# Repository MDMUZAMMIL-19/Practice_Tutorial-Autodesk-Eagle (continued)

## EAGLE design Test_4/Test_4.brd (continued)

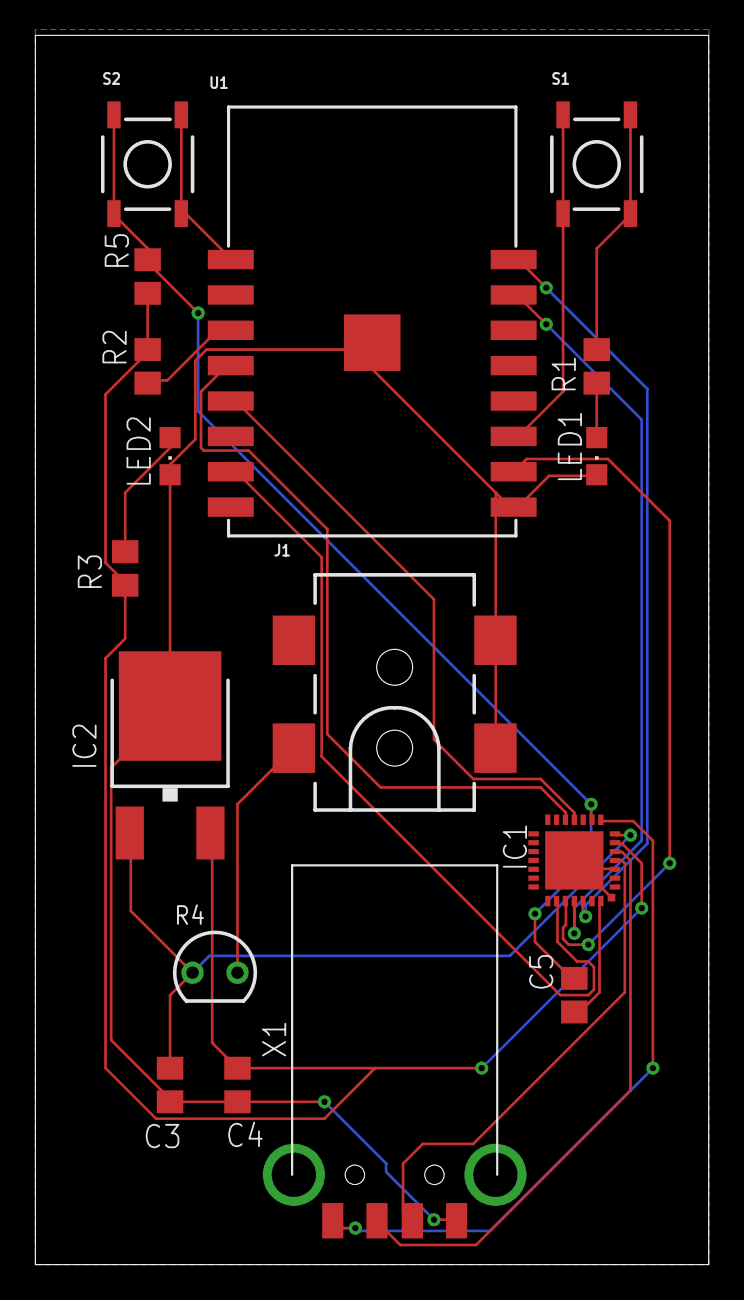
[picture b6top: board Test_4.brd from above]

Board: 2 copper layers, 38.1 x 69.5 mm, 17 parts (0 on the bottom side), 22 nets.

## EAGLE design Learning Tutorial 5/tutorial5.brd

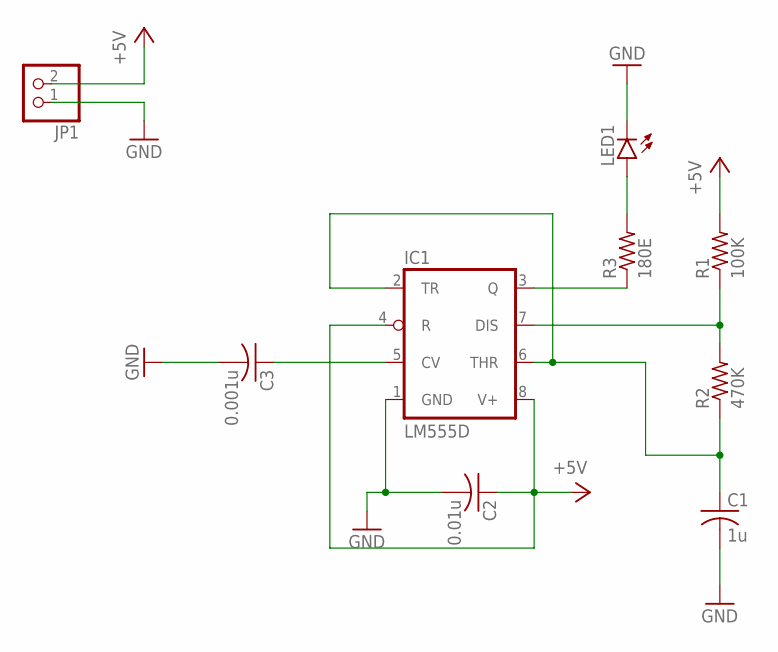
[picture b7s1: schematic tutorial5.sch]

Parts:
C1: 1u; C0805
C2: 0.01u; C0805
C3: 0.001u; C0805
IC1: LM555D; SO08
JP1: PINHD-1X2; 1X02
LED1: LED5MM
R1: 100K; R0805
R2: 470K; R0805
R3: 180E; R0805

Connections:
+5V: C2.1, IC1.4 (R), IC1.8 (V+), JP1.2, R1.2
GND: C1.2, C2.2, C3.2, IC1.1 (GND), JP1.1, LED1.K (C)
unnamed: IC1.7 (DIS), R1.1, R2.2
unnamed: C1.1, IC1.2 (TR), IC1.6 (THR), R2.1
unnamed: IC1.3 (Q), R3.1
unnamed: LED1.A, R3.2
unnamed: C3.1, IC1.5 (CV)

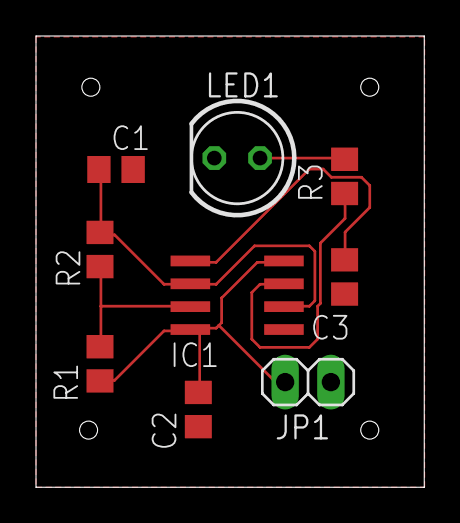
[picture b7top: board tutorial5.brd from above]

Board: 2 copper layers, 21.6 x 25.1 mm, 9 parts (0 on the bottom side), 7 nets.

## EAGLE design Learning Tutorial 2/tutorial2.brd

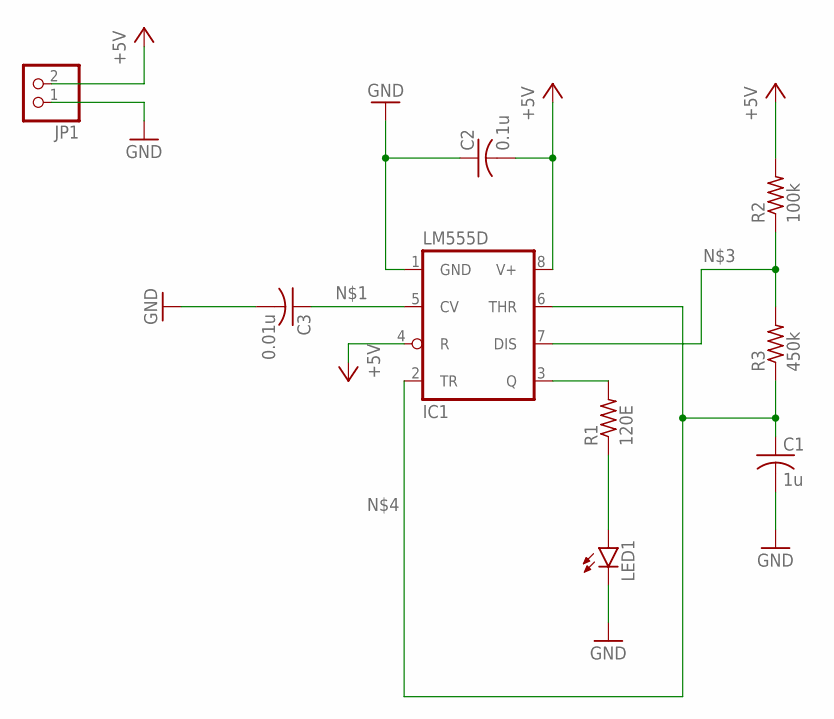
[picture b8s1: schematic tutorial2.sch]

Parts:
C1: 1u; C0805
C2: 0.1u; C0805
C3: 0.01u; C0805
IC1: LM555D; SO08
JP1: PINHD-1X2; 1X02
LED1: LED5MM
R1: 120E; R0805
R2: 100k; R0805
R3: 450k; R0805

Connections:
+5V: C2.2, IC1.4 (R), IC1.8 (V+), JP1.2, R2.2
GND: C1.2, C2.1, C3.2, IC1.1 (GND), JP1.1, LED1.K (C)
unnamed: C3.1, IC1.5 (CV)
unnamed: IC1.3 (Q), R1.2
unnamed: IC1.7 (DIS), R2.1, R3.2
unnamed: C1.1, IC1.2 (TR), IC1.6 (THR), R3.1
unnamed: LED1.A, R1.1

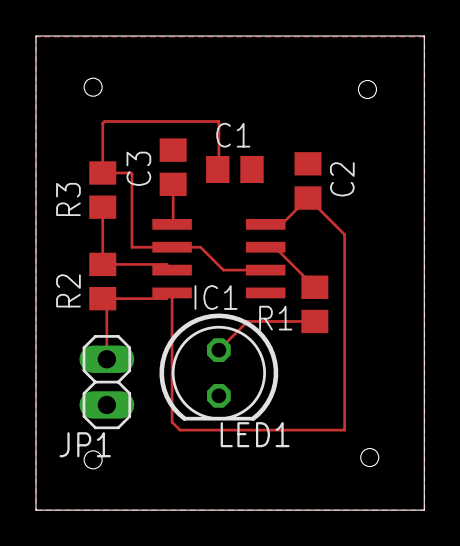
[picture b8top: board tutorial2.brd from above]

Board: 2 copper layers, 21.6 x 26.3 mm, 9 parts (0 on the bottom side), 7 nets.
